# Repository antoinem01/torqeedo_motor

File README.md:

# Torqeedo motor

Arduino sketch that drives a Torqeedo motor over RS485, with a potentiometer for speed control and two safety switches (emergency stop and dead man switch).

## Documentation

- [Torqeedo 1103CL aansturing](docs/torqeedo-1103cl-aansturing.md)
- [Bench-test checklist](docs/bench-test-checklist.md)
- [IP68 & trillingsbestendige opbouw](docs/ip68-robuuste-opbouw.md)
- [Geïntegreerde PCB (alles op één print)](docs/pcb-geintegreerd.md)
- [KiCad-project: schema + printontwerp](hardware/kicad/README.md)

## Hardware

Components:

- Arduino Uno
- MAX485 TTL-RS485 module
- Potentiometer (speed control)
- Emergency stop button (normally closed)
- Dead man switch (normally open)
- Torqeedo Travel 1103 CL motor

Pins:

- `2` — RS485 TX (to MAX485 `DI`)
- `3` — RS485 RX (to MAX485 `RO`)
- `4` — RS485 DE (driver enable, to MAX485 `DE`+`RE`)
- `A0` — potentiometer wiper (speed control)
- `5` — emergency stop (normally closed button between pin and GND)
- `6` — dead man switch (normally open button between pin and GND)

### System diagram

Intended full setup, powered from the Torqeedo battery pack:

```mermaid
graph TD
    BAT["Torqeedo battery 29.6V<br/>(built-in BMS: overcharge/<br/>short-circuit/deep-discharge protection)"]
    SW["Main switch / pull-out plug"]
    FUSE1["Fuse ~40A<br/>(motor circuit)"]
    FUSE2["Fuse ~1A<br/>(logic circuit)"]
    MOTOR["Torqeedo Travel 1103 CL motor"]
    BUCK["DC-DC buck converter<br/>29.6V to 5-9V"]
    UNO["Arduino Uno"]
    TTL["MAX485 TTL-RS485 module"]
    POT["Potentiometer (A0)"]
    ESTOP["Emergency stop (pin 5)"]
    DMAN["Dead man switch (pin 6)"]

    BAT --> SW
    SW --> FUSE1 --> MOTOR
    SW --> FUSE2 --> BUCK --> UNO
    UNO -- "TX / RX / DE" --> TTL
    TTL -- "RS485 A/B twisted pair" --> MOTOR
    POT --> UNO
    ESTOP --> UNO
    DMAN --> UNO
    BAT -. "common ground" .- UNO
    BAT -. "common ground" .- TTL
```

Notes:

- Two **separate fuses**: a heavy one (~40A) for the motor circuit and a small one
  (~1A) for the logic circuit. A single shared fuse is risky — a motor current
  spike could take down the Arduino's power too.
- The Uno is powered from the same battery as the motor, via a DC-DC buck
  converter (29.6V → 5-9V), not from an independent power source.
- A main switch / pull-out plug in front of everything lets you fully de-energize
  the system, independent of the software emergency stop on pin 5.
- The battery, Uno and TTL module must share a **common ground** — easy to
  forget, but required for the RS485 signal reference to work reliably.

### RS485 wiring

A cheap MAX485 breakout module is used to convert the Arduino's UART signal to the
RS485 bus. On these modules DE and RE are usually tied together, so a single
Arduino pin can drive both:

| Arduino Uno | MAX485 module     |
| ----------- | ------------------ |
| `5V`        | `VCC`               |
| `GND`       | `GND`               |
| `2` (TX)    | `DI`                 |
| `3` (RX)    | `RO`                 |
| `4` (DE)    | `DE` + `RE` (tied together) |
| —           | `A` / `B` → to the Torqeedo RS485 bus |

Check the `A`/`B` polarity against the Torqeedo motor's connector documentation —
if the motor doesn't respond, try swapping `A` and `B`.

### Torqeedo model

Target motor: **Torqeedo Travel 1103 CL** (long-shaft).

**Status: validated against the real motor** (bench test, 2026-07-25). The sketch
was tested against an actual Travel 1103 CL powered from an adjustable DC supply
at 29 V, propeller in air (no load). The motor's controller drew ~0.06 A idle,
responded to throttle, and the propeller ran both **forward and reverse** as
commanded. The RS485 protocol (based on ArduPilot's `AP_Torqeedo`) works against
this model and firmware.

This validation was **no-load only**. The current bench rig is a breadboard
lash-up, not a robust install, and the on-water power topology (buck converter,
fuses, main switch) has not been built or tested yet. Keep testing carefully,
without load, before relying on it on the water.

### ⚠️ Safety

This sketch controls a real motor, potentially on a boat. Bugs, wiring mistakes,
or protocol misunderstandings can cause unexpected motor behavior. Always:

- Test on the bench, out of the water, with the propeller removed or the boat secured, before any on-water use.
- Verify the emergency stop and dead man switch actually cut power before trusting them.
- Use at your own risk — this project comes with **no warranty**, see [LICENSE](LICENSE).

## How it works

- Reads the potentiometer and drives the motor via an RS485 protocol with a CRC8 checksum.
- Speed is ramped up/down gradually (soft start/stop, max 10 units per 100 ms).
- The motor stops immediately on emergency stop or when the dead man switch is released.
- A watchdog timer (2 s) restarts the Arduino if the loop hangs.
- The number of errors/stops is tracked in EEPROM.

## Libraries

Only standard Arduino libraries are needed, no external dependencies:

- `SoftwareSerial`
- `EEPROM`
- `avr/wdt`

## Uploading

Open `Torqeedo_motor/Torqeedo_motor.ino` in the Arduino IDE (or use `arduino-cli`), select board **Arduino Uno**, and upload.

## Credits

The RS485 bus protocol (framing bytes `0xAC`/`0xAD`/`0xAE`, CRC8 checksum) is based on
[ArduPilot's `AP_Torqeedo` driver](https://github.com/ArduPilot/ardupilot/tree/master/libraries/AP_Torqeedo).
Many thanks to the ArduPilot project for documenting and implementing the Torqeedo bus protocol.

## License

GPLv3, see [LICENSE](LICENSE) — inherited from ArduPilot's GPLv3-licensed `AP_Torqeedo` driver, on which the protocol implementation is based.

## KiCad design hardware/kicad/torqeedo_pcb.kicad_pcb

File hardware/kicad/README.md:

# KiCad-project — geïntegreerde besturingsprint

Schema **en** printontwerp voor de geïntegreerde besturingsprint uit
[`../../docs/pcb-geintegreerd.md`](../../docs/pcb-geintegreerd.md).

## Bestanden

| Bestand | Inhoud |
|---|---|
| `torqeedo_pcb.kicad_pro` | projectbestand — **open dit in KiCad** |
| `torqeedo_pcb.kicad_sch` | schema (netlist, footprints toegewezen) |
| `torqeedo_pcb.kicad_pcb` | **printontwerp: geplaatst, gerouteerd, massavlakken** |
| `fab/` | Gerbers + boorbestanden (`*-gerbers.zip`), BOM, plaatsingsbestand |
| `pcb-top.png` / `pcb-bottom.png` | 3D-weergave van boven- en onderkant |
| `ps1-buck-gauge.html` | pagina met de printweergaven + het meetvel voor PS1 |
| `ps1-buck-gauge.svg` | alleen het meetvel — **printen op 100 %**, schaal 1:1 |
| `tools/` | de scripts die deze print uit het schema genereren — zie [`tools/README.md`](tools/README.md) |

De symbolen zijn **in het schema ingebed**; de footprints komen uit de
**standaard KiCad-bibliotheken** (KiCad 9). Geen externe libraries nodig.

## De print

| | |
|---|---|
| Formaat | **100 × 80 mm**, 2 lagen, 1,6 mm |
| Montage | 4× **M3** (⌀3,2 mm) op 5 mm van elke hoek |
| Koperlagen | **F.Cu** = signalen, **B.Cu** = doorlopend **massavlak** (92,8 % dicht, één eiland) |
| Baanbreedtes | 0,25 mm signaal · 0,50 mm +5 V/GND · 0,80 mm +12 V |
| Via's | 0,7 mm pad / 0,35 mm boring — 32 stuks, waarvan 15 stitching-via's naar het massavlak |
| Clearance | 0,25 mm (netclasses `Default` / `Power` / `HV` staan in het projectbestand) |

De onderlaag is bewust bijna onaangeroerd gelaten: alleen een handvol korte
oversteekjes, zodat het massavlak een **aaneengesloten retourpad** blijft.

## Indeling

```
 ┌──────────────────────────────────────────────────────────┐
 │  SW1  C13   J_FTDI                          J_PWR  D1    │  ← 12 V in, ompoling
 │                                        C1        ┌─────┐ │
 │ J_RS485  TVS1  JP_*   U1      U2    R6/C4/R7  C2 │BUCK │ │  ← 12 V→5 V module
 │   A/B/G  R1-R3        MAX485  ATmega  C11        │PS1  │ │     (ruimte vrij)
 │                       C3      328P    L1/C10     └─────┘ │
 │                   C7 Y1 C8            J_ISP              │
 │ J_ESTOP    C5/C6  R4/R5                                  │
 │ J_DMAN                     J_POT                         │
 │            TORQEEDO 1103 CL - BESTURING  rev A           │
 └──────────────────────────────────────────────────────────┘
```

De plaatsing volgt de aandachtspunten uit
[`pcb-geintegreerd.md` §11](../../docs/pcb-geintegreerd.md):

- **Kristal Y1 staat pal tegen pin 9/10** van de ATmega — XTAL1 is 9,1 mm en
  XTAL2 10,0 mm lang, beide zonder via, met C7/C8 er direct naast.
- **Ontkoppeling tegen de voedingspinnen:** C9 bij VCC (pin 7), C3 bij MAX485
  pin 8, L1+C10 (AVCC-filter) direct bij pin 20, C11 bij AREF.
- **Analoge tak kort en ver van de buck:** C4/R6/R7 staan tegen pin 23; de
  A0-baan loopt op **40,9 mm** van de buck-module en 18,3 mm van het
  12 V-koper.
- **RS485 bij de connector:** terminatie (R1/JP_TERM), bias (R2/R3/JP_BA/JP_BB)
  en TVS1 staan tussen U1 en J_RS485; A en B lopen als paar.
- **Voedingsscheiding:** J_PWR, D1, C1 en de buck zitten samen in de
  rechterbovenhoek, gescheiden van de 5 V-logica en de A0-lijn.
- **Veldbedrading** (RS485, potmeter, noodstop, dode man) zit aan de linker- en
  onderrand; **programmeerheaders** (J_FTDI, J_ISP) liggen vrij bereikbaar.

Op de silkscreen staan de aansluitingen benoemd (`+12V`/`GND`, `A`/`B`/`GND`,
`POT`, `E-STOP`, `DODE MAN`, `IN+`/`IN-`/`+5V`/`GND`, `DTR TX RX 5V G G`), plus
het gereserveerde vlak voor de buck-module.

## Verificatiestatus

Gecontroleerd met KiCad 9.0.2:

- **DRC: 0 overtredingen, 0 onverbonden items** (inclusief silkscreen- en
  afbakeningsregels).
- **Netlist print = netlist schema:** alle **114 pad-net-verbindingen** en 39
  componenten komen exact overeen; geen footprint-afwijkingen.
- Alle silkscreen-tekst valt binnen de bordrand.

> Dit is een **ontwerp-verificatie, geen gebouwde print.** Zie hieronder wat je
> vóór bestellen zelf moet nakijken.

## Nakijken vóór je bestelt

1. **PS1 buck-module — moet hoe dan ook nog veranderen.** De 1×4 header is een
   *placeholder* uit het schema: vier pads op één rij, 2,54 mm, 7,62 mm totaal.
   Een MP1584EN-achtige module zet het ingangspaar aan de ene kant van een 22 mm
   print en het uitgangspaar aan de andere — dat past daar niet in. Dit is dus een
   **nieuwe footprint**, geen omgewisselde pinvolgorde.

   Er is geen betrouwbare maatvoering te vinden: verkopers noemen allemaal
   22 × 17 × 4 mm, maar **niemand publiceert gatposities**, en ze verschillen per
   batch. Meet daarom je eigen module met
   [`ps1-buck-gauge.svg`](ps1-buck-gauge.svg) — print op **100 %** (niet
   "passend maken"), controleer eerst de kalibratiebalk op 100,0 mm, en lees op
   het 1 mm-raster de vier gatposities af.

   Het silkscreen-kader (20 × 16 mm) is de ruimte die de module nu krijgt.
2. **TVS1 SM712** — aangenomen SOT-23-pinout is pin 1 = A, 2 = GND, 3 = B.
   Controleer tegen het datasheet (optioneel onderdeel, dus laag risico).
3. **D1** — kathode (band) hoort aan de `+12V_PROT`-kant; zo is hij bedraad,
   controleer de silk-oriëntatie.
4. **C2/C12 (10 µF)** staan als keramisch 0805. Wil je elco's, wijs dan
   `CP_Radial` toe en let op polariteit.
5. **J_FTDI VCC** — laat los als de print al via de buck gevoed wordt
   (zie [`pcb-geintegreerd.md` §5](../../docs/pcb-geintegreerd.md)).

## Fabricagebestanden opnieuw maken

```sh
kicad-cli pcb export gerbers --no-protel-ext \
  --layers F.Cu,B.Cu,F.Mask,B.Mask,F.Silkscreen,B.Silkscreen,F.Paste,Edge.Cuts \
  -o fab/ torqeedo_pcb.kicad_pcb
kicad-cli pcb export drill --format excellon --excellon-separate-th -o fab/ torqeedo_pcb.kicad_pcb
kicad-cli pcb export pos --format csv --units mm --side both -o fab/torqeedo_pcb-pos.csv torqeedo_pcb.kicad_pcb
kicad-cli pcb drc --severity-error --severity-warning torqeedo_pcb.kicad_pcb
```

`fab/torqeedo_pcb-gerbers.zip` is wat je bij een fabrikant (JLCPCB, Aisler,
Eurocircuits) uploadt. Standaard 2-laags 1,6 mm proces; de kleinste maten op de
print (0,25 mm baan, 0,35 mm boring) zitten ruim binnen wat iedereen aankan.

## Bekende oneffenheid

De referenties `J_PWR`, `J_POT`, `JP_BA`, … eindigen niet op een cijfer. KiCad
ziet zulke namen als **niet-geannoteerd** en meldt dat bij het openen van het
schema; in de BOM verschijnen ze als `J_PWR?`. Dat is **cosmetisch** — netlist,
print en fabricagebestanden zijn correct (de print gebruikt de namen zonder
`?`). Wil je het weg hebben, hernoem dan in het schema naar bijvoorbeeld
`J_PWR1`; dan moeten de verwijzingen in `docs/pcb-geintegreerd.md` mee.

---

## Waar we gebleven zijn

De print is **af en geverifieerd** (DRC 0/0, netlist gelijk aan het schema) en
staat als `pcb-rev-A` in git. Hij is **nog niet besteld**, en dat moet ook nog
niet: er is één openstaand punt.

**Geblokkeerd op:** de vier gatposities van jouw buck-module. PS1 heeft nu een
placeholder-footprint die sowieso niet klopt (zie *Nakijken vóór je bestelt*,
punt 1). Meet de module met [`ps1-buck-gauge.svg`](ps1-buck-gauge.svg) — printen
op 100 %, eerst de kalibratiebalk op 100,0 mm controleren.

**Zodra die vier coördinaten er zijn:**

1. PS1 wordt **twee 1×2-headers** in plaats van één blok, zodat de module in een
   voetje zit en er zonder soldeerbout af kan — op een boot telt dat zwaarder
   dan op een bureau, en korte draadbruggen vangen een millimeter afwijking op.
2. `place.py` (tabel `PLACE`) en het silkscreen-kader in `finish.py` aanpassen.
3. `./tools/regenerate.sh` draaien tot hij schoon is, dan `--install`.
4. Gerbers opnieuw exporteren en taggen als `pcb-rev-B`. `pcb-rev-A` blijft staan.

De overige vier punten uit *Nakijken vóór je bestelt* (TVS1-pinout,
D1-oriëntatie, C2/C12, J_FTDI VCC) zijn nog niet nagelopen.

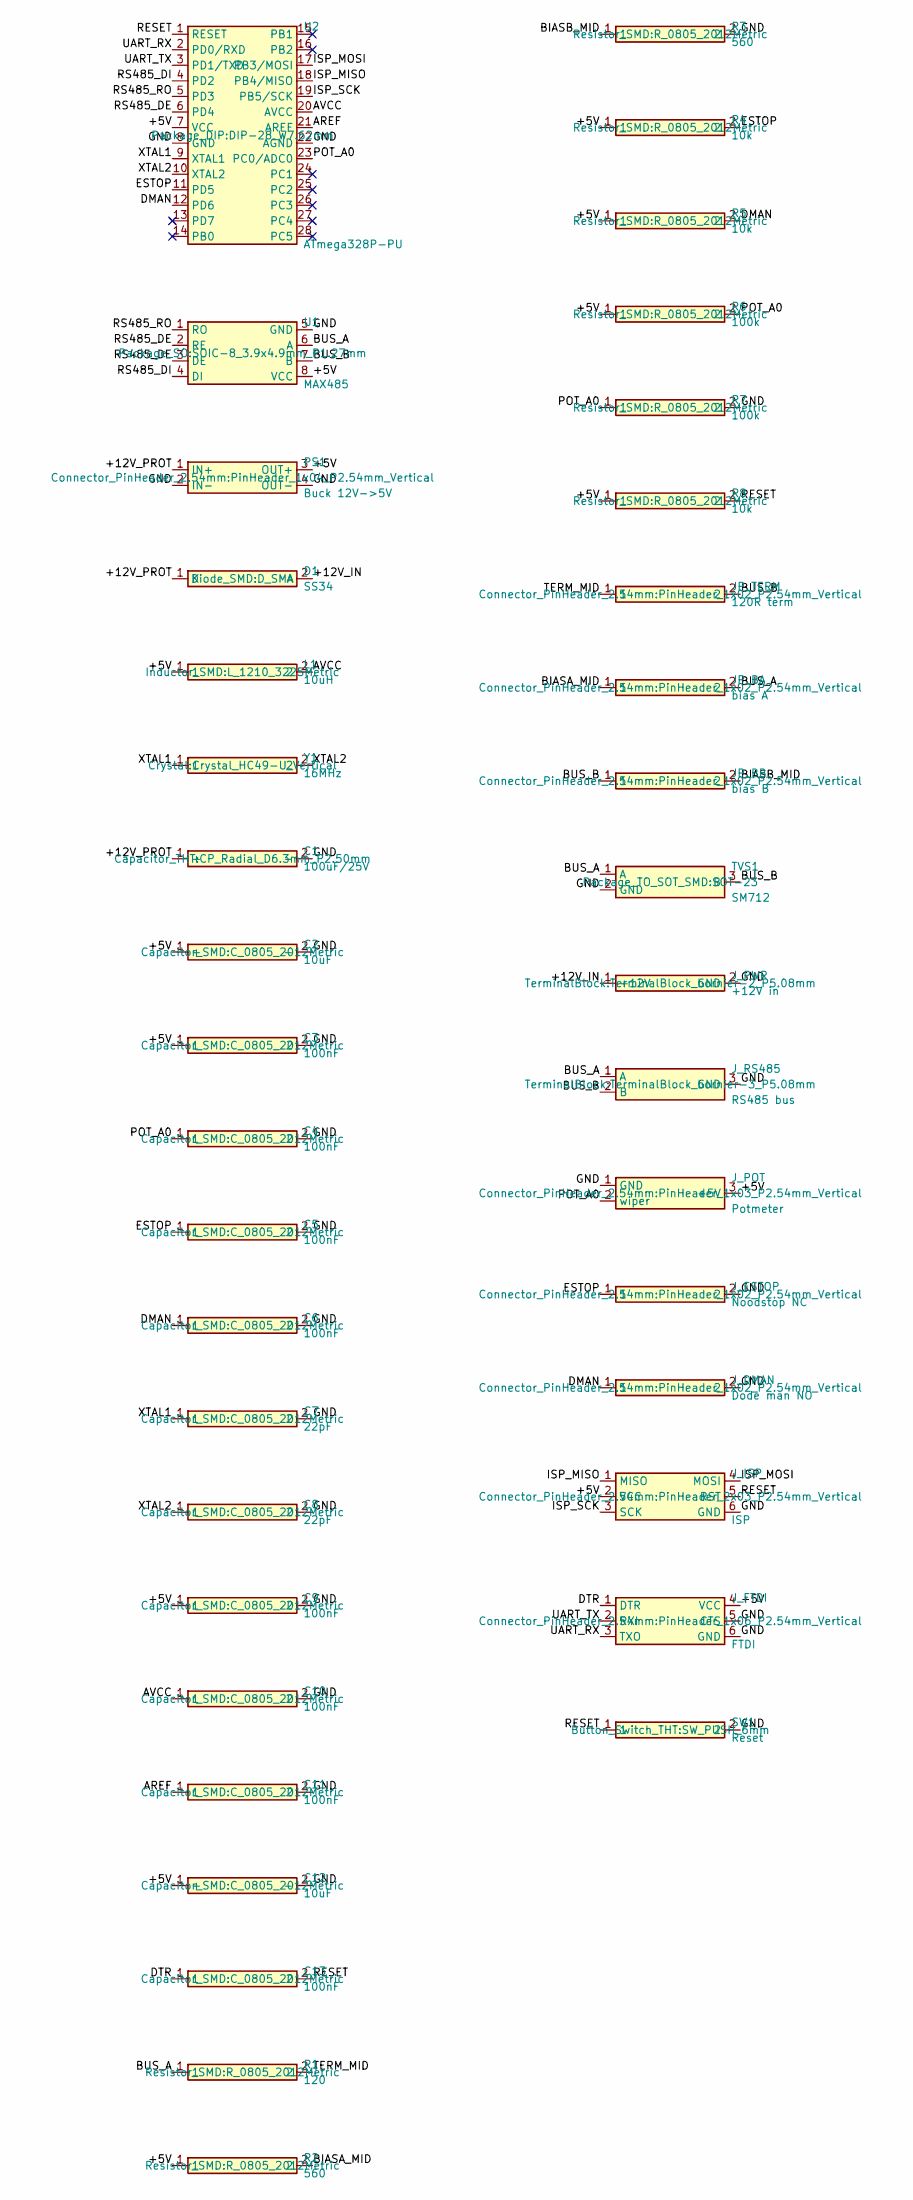
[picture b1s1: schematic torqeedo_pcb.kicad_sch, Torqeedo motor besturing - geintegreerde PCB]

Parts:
C1: 100uF/25V; CP_Radial_D6.3mm_P2.50mm
C2, C12: 10uF; C_0805_2012Metric
C3, C4, C5, C6, C9, C10, C11, C13: 100nF; C_0805_2012Metric
C7, C8: 22pF; C_0805_2012Metric
D1: SS34; D_SMA
JP_BA: bias A; PinHeader_1x02_P2.54mm_Vertical
JP_BB: bias B; PinHeader_1x02_P2.54mm_Vertical
JP_TERM: 120R term; PinHeader_1x02_P2.54mm_Vertical
J_DMAN: Dode man NO; PinHeader_1x02_P2.54mm_Vertical
J_ESTOP: Noodstop NC; PinHeader_1x02_P2.54mm_Vertical
J_FTDI: FTDI; PinHeader_1x06_P2.54mm_Vertical
J_ISP: ISP; PinHeader_2x03_P2.54mm_Vertical
J_POT: Potmeter; PinHeader_1x03_P2.54mm_Vertical
J_PWR: +12V in; TerminalBlock_bornier-2_P5.08mm
J_RS485: RS485 bus; TerminalBlock_bornier-3_P5.08mm
L1: 10uH; L_1210_3225Metric
PS1: Buck 12V->5V; PinHeader_1x04_P2.54mm_Vertical
R1: 120; R_0805_2012Metric
R2, R3: 560; R_0805_2012Metric
R4, R5, R8: 10k; R_0805_2012Metric
R6, R7: 100k; R_0805_2012Metric
SW1: Reset; SW_PUSH_6mm
TVS1: SM712; SOT-23
U1: MAX485; SOIC-8_3.9x4.9mm_P1.27mm
U2: ATmega328P-PU; DIP-28_W7.62mm
Y1: 16MHz; Crystal_HC49-U_Vertical

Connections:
/+5V: C2.1 (+), C3.1, C9.1, C12.1 (+), J_FTDI.4 (VCC), J_ISP.2 (VCC), J_POT.3 (+5V), L1.1, PS1.3 (OUT+), R2.1, R4.1, R5.1, R6.1, R8.1, U1.8 (VCC), U2.7 (VCC)
/+12V_IN: D1.2 (A), J_PWR.1 (+12V)
/+12V_PROT: C1.1 (+), D1.1 (K), PS1.1 (IN+)
/AREF: C11.1, U2.21 (AREF)
/AVCC: C10.1, L1.2, U2.20 (AVCC)
/BIASA_MID: JP_BA.1, R2.2
/BIASB_MID: JP_BB.2, R3.1
/BUS_A: JP_BA.2, J_RS485.1 (A), R1.1, TVS1.1 (A), U1.6 (A)
/BUS_B: JP_BB.1, JP_TERM.2, J_RS485.2 (B), TVS1.3 (B), U1.7 (B)
/DMAN: C6.1, J_DMAN.1, R5.2, U2.12 (PD6)
/DTR: C13.1, J_FTDI.1 (DTR)
/ESTOP: C5.1, J_ESTOP.1, R4.2, U2.11 (PD5)
/GND: C1.2 (-), C2.2 (-), C3.2, C4.2, C5.2, C6.2, C7.2, C8.2, C9.2, C10.2, C11.2, C12.2 (-), J_DMAN.2, J_ESTOP.2, J_FTDI.5 (CTS), J_FTDI.6 (GND), J_ISP.6 (GND), J_POT.1 (GND), J_PWR.2 (GND), J_RS485.3 (GND), PS1.2 (IN-), PS1.4 (OUT-), R3.2, R7.2, SW1.2, TVS1.2 (GND), U1.5 (GND), U2.8 (GND), U2.22 (AGND)
/ISP_MISO: J_ISP.1 (MISO), U2.18 (PB4/MISO)
/ISP_MOSI: J_ISP.4 (MOSI), U2.17 (PB3/MOSI)
/ISP_SCK: J_ISP.3 (SCK), U2.19 (PB5/SCK)
/POT_A0: C4.1, J_POT.2 (wiper), R6.2, R7.1, U2.23 (PC0/ADC0)
/RESET: C13.2, J_ISP.5 (RST), R8.2, SW1.1, U2.1 (RESET)
/RS485_DE: U1.2 (RE), U1.3 (DE), U2.6 (PD4)
/RS485_DI: U1.4 (DI), U2.4 (PD2)
/RS485_RO: U1.1 (RO), U2.5 (PD3)
/TERM_MID: JP_TERM.1, R1.2
/UART_RX: J_FTDI.3 (TXO), U2.2 (PD0/RXD)
/UART_TX: J_FTDI.2 (RXI), U2.3 (PD1/TXD)
/XTAL1: C7.1, U2.9 (XTAL1), Y1.1
/XTAL2: C8.1, U2.10 (XTAL2), Y1.2

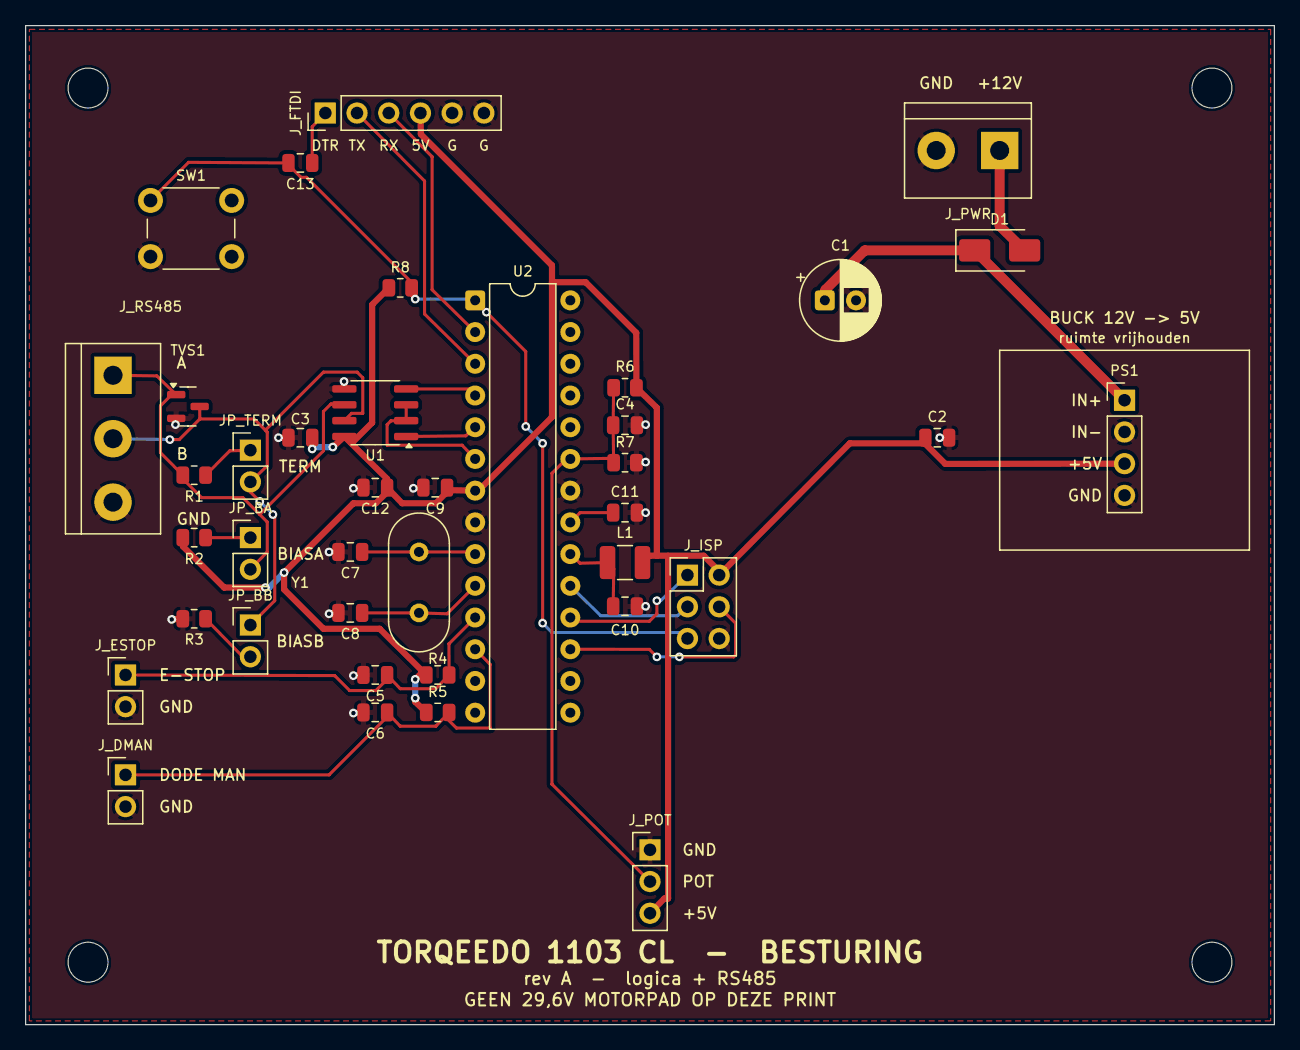
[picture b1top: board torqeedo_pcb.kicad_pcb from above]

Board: 2 copper layers, 100.0 x 80.0 mm, 43 parts (0 on the bottom side), 26 nets.

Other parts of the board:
H1, H2, H3, H4: (no value)

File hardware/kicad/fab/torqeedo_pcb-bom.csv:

"Ref","Waarde","Footprint","Aantal"
"C1","100uF/25V","Capacitor_THT:CP_Radial_D6.3mm_P2.50mm","1"
"C2,C12","10uF","Capacitor_SMD:C_0805_2012Metric","2"
"C3-C6,C9-C11,C13","100nF","Capacitor_SMD:C_0805_2012Metric","8"
"C7,C8","22pF","Capacitor_SMD:C_0805_2012Metric","2"
"D1","SS34","Diode_SMD:D_SMA","1"
"JP_BA?","bias A","Connector_PinHeader_2.54mm:PinHeader_1x02_P2.54mm_Vertical","1"
"JP_BB?","bias B","Connector_PinHeader_2.54mm:PinHeader_1x02_P2.54mm_Vertical","1"
"JP_TERM?","120R term","Connector_PinHeader_2.54mm:PinHeader_1x02_P2.54mm_Vertical","1"
"J_DMAN?","Dode man NO","Connector_PinHeader_2.54mm:PinHeader_1x02_P2.54mm_Vertical","1"
"J_ESTOP?","Noodstop NC","Connector_PinHeader_2.54mm:PinHeader_1x02_P2.54mm_Vertical","1"
"J_FTDI?","FTDI","Connector_PinHeader_2.54mm:PinHeader_1x06_P2.54mm_Vertical","1"
"J_ISP?","ISP","Connector_PinHeader_2.54mm:PinHeader_2x03_P2.54mm_Vertical","1"
"J_POT?","Potmeter","Connector_PinHeader_2.54mm:PinHeader_1x03_P2.54mm_Vertical","1"
"J_PWR?","+12V in","TerminalBlock:TerminalBlock_bornier-2_P5.08mm","1"
"J_RS485","RS485 bus","TerminalBlock:TerminalBlock_bornier-3_P5.08mm","1"
"L1","10uH","Inductor_SMD:L_1210_3225Metric","1"
"PS1","Buck 12V->5V","Connector_PinHeader_2.54mm:PinHeader_1x04_P2.54mm_Vertical","1"
"R1","120","Resistor_SMD:R_0805_2012Metric","1"
"R2,R3","560","Resistor_SMD:R_0805_2012Metric","2"
"R4,R5,R8","10k","Resistor_SMD:R_0805_2012Metric","3"
"R6,R7","100k","Resistor_SMD:R_0805_2012Metric","2"
"SW1","Reset","Button_Switch_THT:SW_PUSH_6mm","1"
"TVS1","SM712","Package_TO_SOT_SMD:SOT-23","1"
"U1","MAX485","Package_SO:SOIC-8_3.9x4.9mm_P1.27mm","1"
"U2","ATmega328P-PU","Package_DIP:DIP-28_W7.62mm","1"
"Y1","16MHz","Crystal:Crystal_HC49-U_Vertical","1"
